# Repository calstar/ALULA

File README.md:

# ALULA (LE2)
 Alula/ LE2 Hot-fire and Flight Vehicle Electronics Control

## Summary
**DAQboard.ino** file commands the ESP32 that reads data from sensors and commands from the COM Board, and sends data in a package to the COM Board.

**COMBoard.ino** file commands the ESP32 that receives data in a package from the DAQ  Board, sends commands to the DAQ Board, and sends data to MATLAB for plotting and data-saving purposes through the serial port.

**liveplot.m** is a MATLAB file that can receive data from the COM Board, create live plots, and save the data.
  1. **Change the test file name according to the trial number in the liveplot.m file.**
  2. Click "Run" to start the code, and close the plotting window to stop the code. Test data will be automatically stored in a spreadsheet under a folder called "**Test_Data_yyyy-mm-dd**."

## ESP32 MAC Addresses
- DAQ Breadboard:{0x24, 0x62, 0xAB, 0xD2, 0x85, 0xDC}
- COM Breadboard:{0xC4, 0xDD, 0x57, 0x9E, 0x91, 0x6C};
- DAQ Protoboard:

## Software requirement
**Ctrl click (Windows) or Cmd click the following links to open them in new tabs**
1. Arduino (https://www.arduino.cc/en/software)
2. MATLAB (https://software.berkeley.edu/matlab®)
    - To control the serial port, you need to install the [**Instrument Control Toolbox**](https://www.mathworks.com/products/instrument.html).
3. (optional) An external code editing software such as Atom (https://atom.io) or Visual Studio (https://visualstudio.microsoft.com/downloads/).
    - Arduino IDE and MATLAB are sufficient for all the coding
4. (recommended) GitHub Desktop (https://desktop.github.com). You can pull, push, and edit files with ease. **Step 3 required if you would like to download GitHub Desktop as the software requires an external editor.**

## How to contribute

### Using Git (recommended)
CLONE USING: 
```git clone --recurse-submodules git@github.com:calstar/LE2.git``` 

Please refer to https://rocketry.gitbook.io/public/tutorials/avionics/git-and-workflow for more information.

A basic workflow might go as follows:

`git status` 

`git add .` 

`git status` Note: if you see files here that are not code/hardware and should not be added (binaries, images, autosave files, etc.), STOP and fix the `.gitignore` 

`git commit -m "[Descriptive commit message of what you changed]"` 

`git push` 

### Using Github Desktop (not recommended)
1. Make sure you have access to this project
    - Check with you administrators
2. Go to the Github app, sign in, and click on the top left corner. You should see a pop-up window with an "Add" button. Select that button and choose "Clone repository."
3. Search in "Filter you repositories" using the keyword "ellie-ground." Select the correct repository and click "Clone."
    - If you want this cloned repository to be in a different folder, change the "Local Path."
4. After you have edited and saved the file in the local repository, GitHub Desktop will detect changes and prompt you to commit. Make sure to double check your changes before committing.
5. On the bottom left corner, put down a short summary that describes what you have changed, then click "Commit to **main**."
6. In the middle of the screen (or on the top banner) you will see "Push commits to the origin remote." If you are sure that the commit is ready, click "Push origin."
6. Check the project online and see if the changes have been reflected.

## Helpful resources
### ESP32-DevkitC/ ESP32-Devkit-v4 (for PCB application - antenna sticks out of board)
Getting started

https://docs.espressif.com/projects/esp-idf/en/latest/esp32/hw-reference/esp32/get-started-devkitc.html

Pinout reference

### ESP32-WROOM/ ESP32-Devkit-v1 (for breadboard/protoboard application - antenna does NOT stick out of board)

Pinout reference

### ESP32-HUZZAH (for breadboard/protoboard application)

Pinout reference

### Pressure transducer color code
Red - E+

Black - E-

Green - A-

White - A+

Other possible combinations: Blue E+; Red E-; Green A-; Black A+

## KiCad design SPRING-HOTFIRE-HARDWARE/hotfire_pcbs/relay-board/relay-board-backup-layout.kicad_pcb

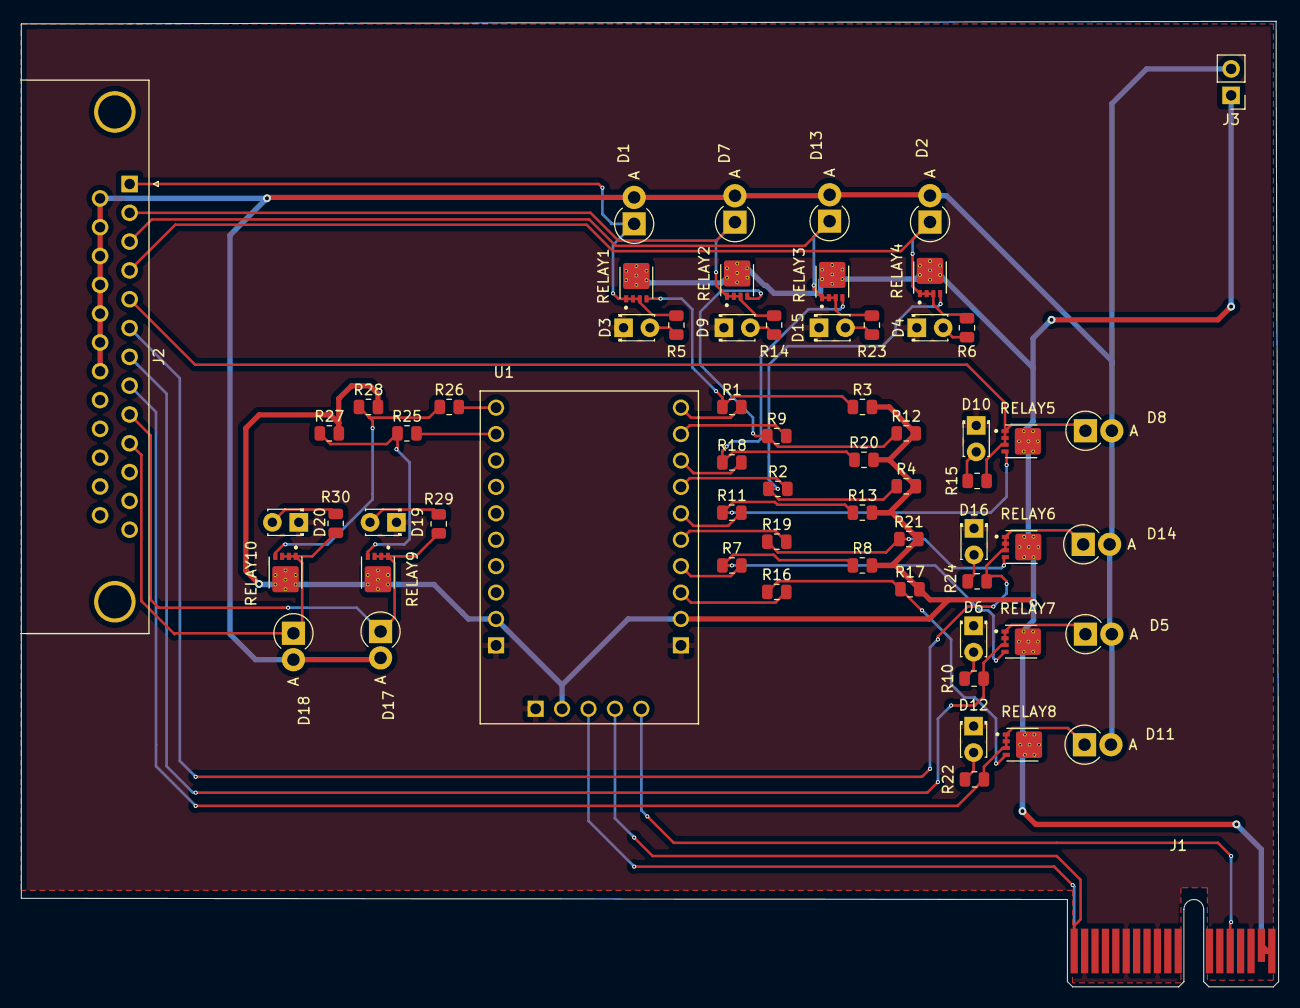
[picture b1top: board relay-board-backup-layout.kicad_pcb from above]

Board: 2 copper layers, 120.9 x 92.8 mm, 64 parts (0 on the bottom side), 47 nets.

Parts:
D1, D2, D5, D7, D8, D11, D13, D14, D17, D18: D_Small; D_DO-15_P2.54mm_Vertical_AnodeUp
D3, D4, D6, D9, D10, D12, D15, D16, D19, D20: LED; LED_D1.8mm_W3.3mm_H2.4mm
J1: PCIE_CONN; BUS_PCIexpress_x1
J2: DB25_Female; DSUB-25_Male_Horizontal_P2.77x2.84mm_EdgePinOffset7.70mm_Ho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
J3: 12V LiPO; PinHeader_1x02_P2.54mm_Vertical
R1, R2, R7, R9, R11, R16, R18, R19, R25, R26: 100; R_0805_2012Metric
R3, R4, R8, R12, R13, R17, R20, R21, R27, R28: 10k; R_0805_2012Metric
R5, R6, R10, R14, R15, R22, R23, R24, R29, R30: 330; R_0805_2012Metric
RELAY1, RELAY2, RELAY3, RELAY4, RELAY5, RELAY6, RELAY7, RELAY8, RELAY9, RELAY10: CSD25402Q3AT; TRANS_CSD25402Q3AT
U1: PCF8575_Breakout

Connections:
+3.3V: J1.B17 (Pin_b17), J1.B18 (Pin_b18)
+5V: J1.A17 (Pin_a17), J1.A18 (Pin_a18), J3.1, R3.2, R4.2, R8.2, R12.2, R13.2, R17.2, R20.2, R21.2, R27.2, R28.2, RELAY1.9, RELAY1.9_1, RELAY1.9_2, RELAY1.9_3, RELAY1.9_4, RELAY1.9_5, RELAY1.9_6, RELAY1.9_7, RELAY2.9, RELAY2.9_1, RELAY2.9_2, RELAY2.9_3, RELAY2.9_4, RELAY2.9_5, RELAY2.9_6, RELAY2.9_7, RELAY3.9, RELAY3.9_1, RELAY3.9_2, RELAY3.9_3, RELAY3.9_4, RELAY3.9_5, RELAY3.9_6, RELAY3.9_7, RELAY4.9, RELAY4.9_1, RELAY4.9_2, RELAY4.9_3, RELAY4.9_4, RELAY4.9_5, RELAY4.9_6, RELAY4.9_7, RELAY5.9, RELAY5.9_1, RELAY5.9_2, RELAY5.9_3, RELAY5.9_4, RELAY5.9_5, RELAY5.9_6, RELAY5.9_7, RELAY6.9, RELAY6.9_1, RELAY6.9_2, RELAY6.9_3, RELAY6.9_4, RELAY6.9_5, RELAY6.9_6, RELAY6.9_7, RELAY7.9, RELAY7.9_1, RELAY7.9_2, RELAY7.9_3, RELAY7.9_4, RELAY7.9_5, RELAY7.9_6, RELAY7.9_7, RELAY8.9, RELAY8.9_1, RELAY8.9_2, RELAY8.9_3, RELAY8.9_4, RELAY8.9_5, RELAY8.9_6, RELAY8.9_7, RELAY9.9, RELAY9.9_1, RELAY9.9_2, RELAY9.9_3, RELAY9.9_4, RELAY9.9_5, RELAY9.9_6, RELAY9.9_7, RELAY10.9, RELAY10.9_1, RELAY10.9_2, RELAY10.9_3, RELAY10.9_4, RELAY10.9_5, RELAY10.9_6, RELAY10.9_7, U1.9 (VDD), U1.12 (VCC), U1.17 (VDD)
/-7V: D1.2 (A), D2.2 (A), D5.2 (A), D7.2 (A), D8.2 (A), D11.2 (A), D13.2 (A), D14.2 (A), D17.2 (A), D18.2 (A), J2.14, J2.15, J2.16, J2.17, J2.18, J2.19, J2.20, J2.21, J2.22, J3.2
GND: D3.1 (K), D4.1 (K), D6.1 (K), D9.1 (K), D10.1 (K), D12.1 (K), D15.1 (K), D16.1 (K), D19.1 (K), D20.1 (K), J1.A2 (Pin_a2), J1.A5 (Pin_a5), J1.A8 (Pin_a8), J1.A11 (Pin_a11), J1.A15 (Pin_a15), J1.B2 (Pin_b2), J1.B6 (Pin_b6), J1.B9 (Pin_b9), J1.B12 (Pin_b12), J1.B16 (Pin_b16), U1.10 (GND), U1.11 (GND), U1.16 (GND)
unnamed: D3.2 (A), R5.2
unnamed: D4.2 (A), R6.2
unnamed: D6.2 (A), R10.2
unnamed: D9.2 (A), R14.2
unnamed: D10.2 (A), R15.2
unnamed: D12.2 (A), R22.2
unnamed: D15.2 (A), R23.2
unnamed: D16.2 (A), R24.2
unnamed: D19.2 (A), R29.2
unnamed: D20.2 (A), R30.2
unnamed: R1.1, R3.1, RELAY1.4
unnamed: R2.1, R4.1, RELAY4.4
unnamed: R7.1, R8.1, RELAY7.4
unnamed: R9.1, R12.1, RELAY2.4
unnamed: R11.1, R13.1, RELAY5.4
unnamed: R16.1, R17.1, RELAY8.4
unnamed: R18.1, R20.1, RELAY3.4
unnamed: R19.1, R21.1, RELAY6.4
unnamed: R25.1, R27.1, RELAY9.4
unnamed: R26.1, R28.1, RELAY10.4
RELAY1: D1.1 (K), J2.1, R5.1, RELAY1.1, RELAY1.2, RELAY1.3
RELAY2: D7.1 (K), J2.2, R14.1, RELAY2.1, RELAY2.2, RELAY2.3
RELAY3: D13.1 (K), J2.3, R23.1, RELAY3.1, RELAY3.2, RELAY3.3
RELAY4: D2.1 (K), J2.4, R6.1, RELAY4.1, RELAY4.2, RELAY4.3
RELAY5: D8.1 (K), J2.5, R15.1, RELAY5.1, RELAY5.2, RELAY5.3
RELAY6: D14.1 (K), J2.6, R24.1, RELAY6.1, RELAY6.2, RELAY6.3
RELAY7: D5.1 (K), J2.7, R10.1, RELAY7.1, RELAY7.2, RELAY7.3
RELAY8: D11.1 (K), J2.8, R22.1, RELAY8.1, RELAY8.2, RELAY8.3
RELAY9: D17.1 (K), J2.9, R29.1, RELAY9.1, RELAY9.2, RELAY9.3
RELAY10: D18.1 (K), J2.10, R30.1, RELAY10.1, RELAY10.2, RELAY10.3
RL INT: J1.B14 (Pin_b14), U1.15 (INT)
RL SCL: J1.B1 (Pin_b1), U1.14 (SCL)
RL SDA: J1.A1 (Pin_a1), U1.13 (SDA)
SIGNAL1: R1.2, U1.25 (P07)
SIGNAL2: R9.2, U1.24 (P06)
SIGNAL3: R18.2, U1.23 (P05)
SIGNAL4: R2.2, U1.22 (P04)
SIGNAL5: R11.2, U1.21 (P03)
SIGNAL6: R19.2, U1.20 (P02)
SIGNAL7: R7.2, U1.19 (P01)
SIGNAL8: R16.2, U1.18 (P00)
SIGNAL9: R25.2, U1.2 (P11)
SIGNAL10: R26.2, U1.1 (P10)

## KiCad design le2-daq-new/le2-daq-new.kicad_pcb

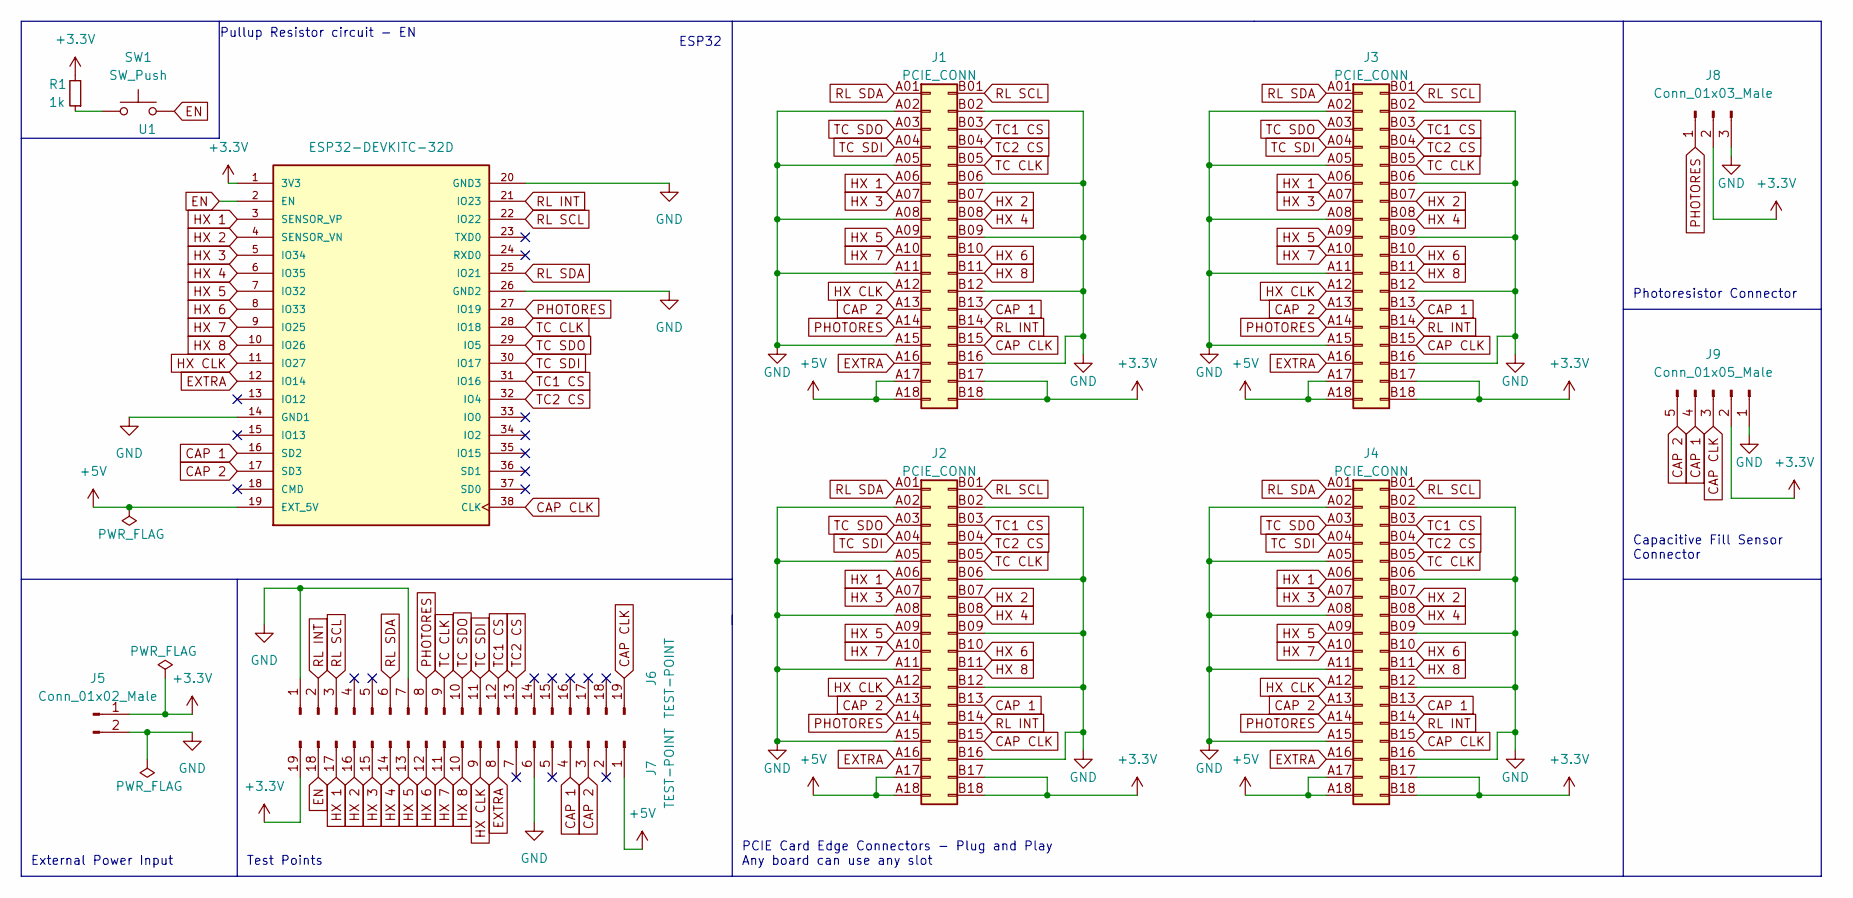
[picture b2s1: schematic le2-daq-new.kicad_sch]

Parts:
J1, J2, J3, J4: PCIE_CONN; AMPHENOL_10018784-10210TLF
J5: Conn_01x02_Male; PinHeader_1x02_P2.54mm_Vertical
J6, J7: TEST-POINT; PinHeader_1x19_P2.54mm_Vertical
J8: Conn_01x03_Male; PinHeader_1x03_P2.54mm_Vertical
J9: Conn_01x05_Male; PinHeader_1x05_P2.54mm_Vertical
R1: 1k; R_0805_2012Metric_Pad1.20x1.40mm_HandSolder
SW1: SW_Push; SolderJumper-2_P1.3mm_Bridged2Bar_Pad1.0x1.5mm
U1: ESP32-DEVKITC-32D; MODULE_ESP32-DEVKITC-32D; PARTREV 4

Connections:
+3.3V: J1.B17 (Pin_b17), J1.B18 (Pin_b18), J2.B17 (Pin_b17), J2.B18 (Pin_b18), J3.B17 (Pin_b17), J3.B18 (Pin_b18), J4.B17 (Pin_b17), J4.B18 (Pin_b18), J5.1, J7.19, J8.2, J9.2, R1.2, U1.1 (3V3)
+5V: J1.A17 (Pin_a17), J1.A18 (Pin_a18), J2.A17 (Pin_a17), J2.A18 (Pin_a18), J3.A17 (Pin_a17), J3.A18 (Pin_a18), J4.A17 (Pin_a17), J4.A18 (Pin_a18), J7.1, U1.19 (EXT_5V)
CAP 1: J1.B13 (Pin_b13), J2.B13 (Pin_b13), J3.B13 (Pin_b13), J4.B13 (Pin_b13), J7.4, J9.4, U1.16 (SD2)
CAP 2: J1.A13 (Pin_a13), J2.A13 (Pin_a13), J3.A13 (Pin_a13), J4.A13 (Pin_a13), J7.3, J9.5, U1.17 (SD3)
CAP CLK: J1.B15 (Pin_b15), J2.B15 (Pin_b15), J3.B15 (Pin_b15), J4.B15 (Pin_b15), J6.19, J9.3, U1.38 (CLK)
EN: J7.18, SW1.2, U1.2 (EN)
EXTRA: J1.A16 (Pin_a16), J2.A16 (Pin_a16), J3.A16 (Pin_a16), J4.A16 (Pin_a16), J7.8, U1.12 (IO14)
GND: J1.A02 (Pin_a2), J1.A05 (Pin_a5), J1.A08 (Pin_a8), J1.A11 (Pin_a11), J1.A15 (Pin_a15), J1.B02 (Pin_b2), J1.B06 (Pin_b6), J1.B09 (Pin_b9), J1.B12 (Pin_b12), J1.B16 (Pin_b16), J2.A02 (Pin_a2), J2.A05 (Pin_a5), J2.A08 (Pin_a8), J2.A11 (Pin_a11), J2.A15 (Pin_a15), J2.B02 (Pin_b2), J2.B06 (Pin_b6), J2.B09 (Pin_b9), J2.B12 (Pin_b12), J2.B16 (Pin_b16), J3.A02 (Pin_a2), J3.A05 (Pin_a5), J3.A08 (Pin_a8), J3.A11 (Pin_a11), J3.A15 (Pin_a15), J3.B02 (Pin_b2), J3.B06 (Pin_b6), J3.B09 (Pin_b9), J3.B12 (Pin_b12), J3.B16 (Pin_b16), J4.A02 (Pin_a2), J4.A05 (Pin_a5), J4.A08 (Pin_a8), J4.A11 (Pin_a11), J4.A15 (Pin_a15), J4.B02 (Pin_b2), J4.B06 (Pin_b6), J4.B09 (Pin_b9), J4.B12 (Pin_b12), J4.B16 (Pin_b16), J5.2, J6.1, J6.7, J7.6, J8.3, J9.1, U1.14 (GND1), U1.20 (GND3), U1.26 (GND2)
HX 1: J1.A06 (Pin_a6), J2.A06 (Pin_a6), J3.A06 (Pin_a6), J4.A06 (Pin_a6), J7.17, U1.3 (SENSOR_VP)
HX 2: J1.B07 (Pin_b7), J2.B07 (Pin_b7), J3.B07 (Pin_b7), J4.B07 (Pin_b7), J7.16, U1.4 (SENSOR_VN)
HX 3: J1.A07 (Pin_a7), J2.A07 (Pin_a7), J3.A07 (Pin_a7), J4.A07 (Pin_a7), J7.15, U1.5 (IO34)
HX 4: J1.B08 (Pin_b8), J2.B08 (Pin_b8), J3.B08 (Pin_b8), J4.B08 (Pin_b8), J7.14, U1.6 (IO35)
HX 5: J1.A09 (Pin_a9), J2.A09 (Pin_a9), J3.A09 (Pin_a9), J4.A09 (Pin_a9), J7.13, U1.7 (IO32)
HX 6: J1.B10 (Pin_b10), J2.B10 (Pin_b10), J3.B10 (Pin_b10), J4.B10 (Pin_b10), J7.12, U1.8 (IO33)
HX 7: J1.A10 (Pin_a10), J2.A10 (Pin_a10), J3.A10 (Pin_a10), J4.A10 (Pin_a10), J7.11, U1.9 (IO25)
HX 8: J1.B11 (Pin_b11), J2.B11 (Pin_b11), J3.B11 (Pin_b11), J4.B11 (Pin_b11), J7.10, U1.10 (IO26)
HX CLK: J1.A12 (Pin_a12), J2.A12 (Pin_a12), J3.A12 (Pin_a12), J4.A12 (Pin_a12), J7.9, U1.11 (IO27)
unnamed: R1.1, SW1.1
PHOTORES: J1.A14 (Pin_a14), J2.A14 (Pin_a14), J3.A14 (Pin_a14), J4.A14 (Pin_a14), J6.8, J8.1, U1.27 (IO19)
RL INT: J1.B14 (Pin_b14), J2.B14 (Pin_b14), J3.B14 (Pin_b14), J4.B14 (Pin_b14), J6.2, U1.21 (IO23)
RL SCL: J1.B01 (Pin_b1), J2.B01 (Pin_b1), J3.B01 (Pin_b1), J4.B01 (Pin_b1), J6.3, U1.22 (IO22)
RL SDA: J1.A01 (Pin_a1), J2.A01 (Pin_a1), J3.A01 (Pin_a1), J4.A01 (Pin_a1), J6.6, U1.25 (IO21)
TC1 CS: J1.B03 (Pin_b3), J2.B03 (Pin_b3), J3.B03 (Pin_b3), J4.B03 (Pin_b3), J6.12, U1.31 (IO16)
TC2 CS: J1.B04 (Pin_b4), J2.B04 (Pin_b4), J3.B04 (Pin_b4), J4.B04 (Pin_b4), J6.13, U1.32 (IO4)
TC CLK: J1.B05 (Pin_b5), J2.B05 (Pin_b5), J3.B05 (Pin_b5), J4.B05 (Pin_b5), J6.9, U1.28 (IO18)
TC SDI: J1.A04 (Pin_a4), J2.A04 (Pin_a4), J3.A04 (Pin_a4), J4.A04 (Pin_a4), J6.11, U1.30 (IO17)
TC SDO: J1.A03 (Pin_a3), J2.A03 (Pin_a3), J3.A03 (Pin_a3), J4.A03 (Pin_a3), J6.10, U1.29 (IO5)

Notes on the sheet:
Capacitive Fill Sensor Connector
Pullup Resistor circuit - EN
Test Points
ESP32
Photoresistor Connector
External Power Input
PCIE Card Edge Connectors - Plug and Play Any board can use any slot

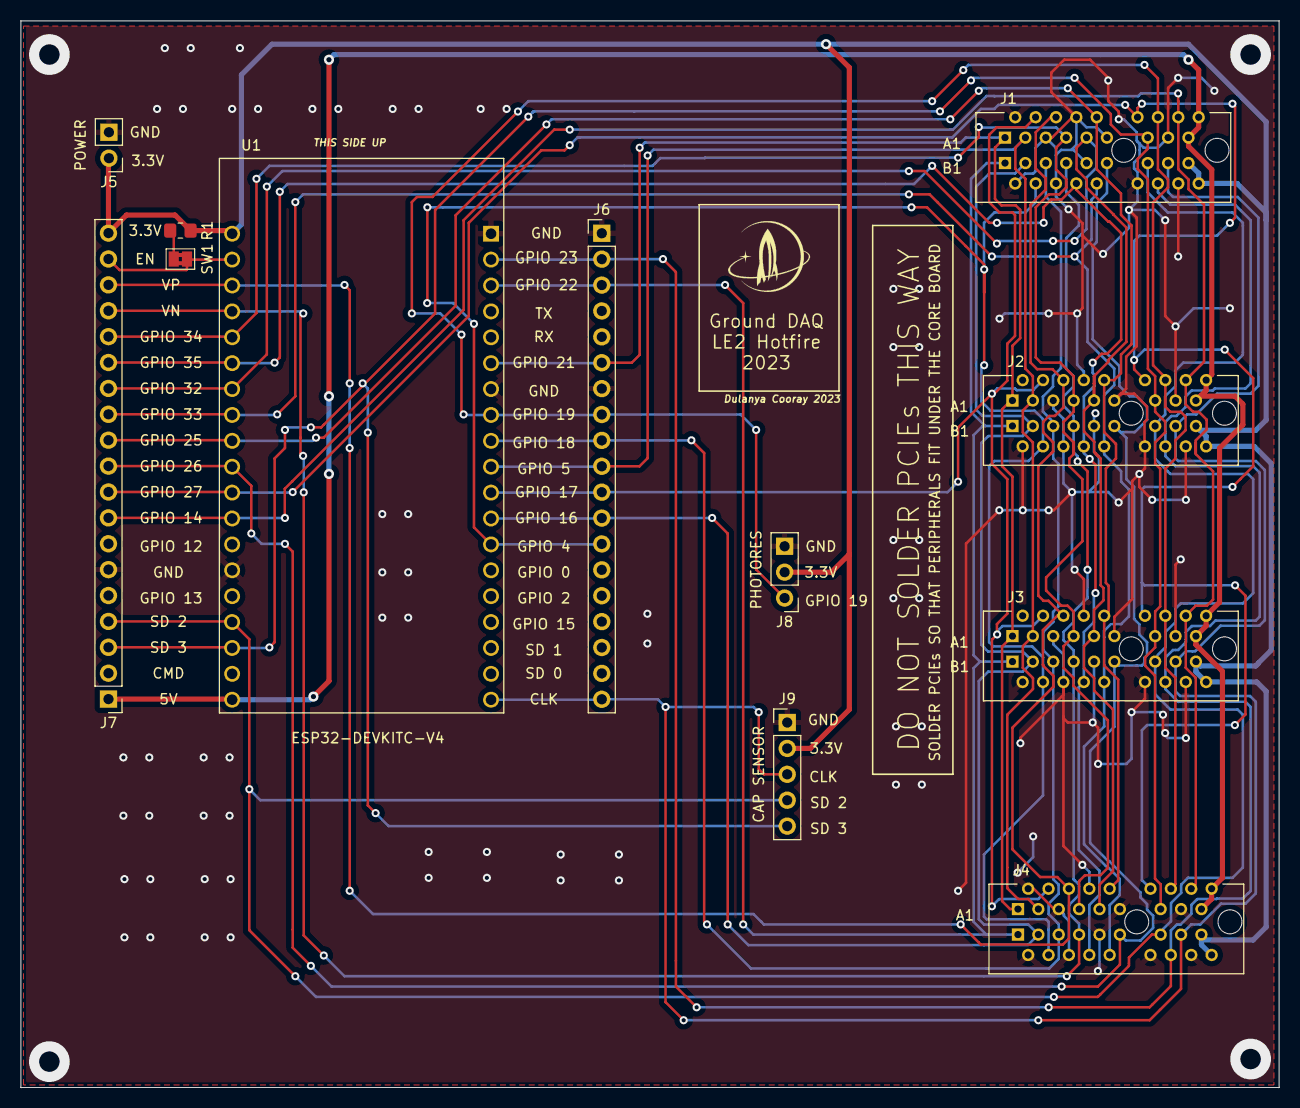
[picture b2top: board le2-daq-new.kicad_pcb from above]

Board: 2 copper layers, 123.4 x 104.6 mm, 12 parts (0 on the bottom side), 27 nets.

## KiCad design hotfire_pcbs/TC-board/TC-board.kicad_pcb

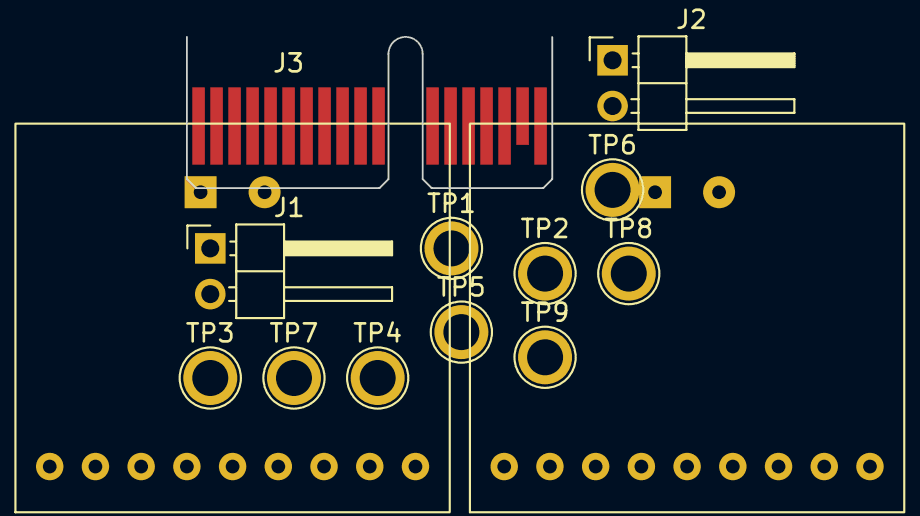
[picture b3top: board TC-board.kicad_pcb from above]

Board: 2 copper layers, 14 parts (0 on the bottom side), 11 nets, no tracks yet.

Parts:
J1, J2: JST; PinHeader_1x02_P2.54mm_Horizontal
J3: PCIE-LP-01-01-F-DV-A-TR; BUS_PCIexpress_x1
TP1, TP2, TP3, TP4, TP5, TP6, TP7, TP8, TP9: TestPoint; TestPoint_Plated_Hole_D2.0mm
U1, U2: MAX31856_Breakout

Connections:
+3V3: J3.B17, J3.B18, U1.11 (VIN), U2.11 (VIN)
/SPI_CS_0: J3.B3, TP8.1, U1.5 (CS)
/SPI_CS_1: J3.B4, TP9.1, U2.5 (CS)
/SPI_MISO: J3.A3, TP5.1, U1.7 (SDO), U2.7 (SDO)
/SPI_MOSI: J3.A4, TP6.1, U1.6 (SDI), U2.6 (SDI)
/SPI_SCK: J3.B5, TP7.1, U1.8 (SCK), U2.8 (SCK)
/TC1_T+: J1.2, TP2.1, U1.2 (T+)
/TC1_T-: J1.1, TP1.1, U1.1 (T-)
/TC2_T+: J2.2, TP4.1, U2.2 (T+)
/TC2_T-: J2.1, TP3.1, U2.1 (T-)
GND: J3.A2, J3.A5, J3.A8, J3.A11, J3.A15, J3.A18, J3.B2, J3.B6, J3.B9, J3.B12, J3.B16, U1.9 (GND), U2.9 (GND)

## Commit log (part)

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2023-06-20 reorganized simulation stuff
2023-06-21 Inaccurate
2023-06-24 updated pcb designs
2023-06-25 flught sim
2023-06-25 added integration code
2023-06-25 skeletal for guesstimator
2023-06-26 Updated flight sim
2023-06-26 .eng file header updated
2023-07-02 Add files via upload
    implemented vers
2023-07-20 liam_thrustcurve
    Working on thrust curve convergent model
2023-07-22 Fixed Thrust Curve
    Solved Convergence
    Added failure errors for flow instability - baseline 10% pressure drop requirement
2023-07-22 Added GN2
    Gamma = Cp/Cv
2023-07-24 feed system resistance
2023-07-24 main input
2023-07-24 .eng attempt. Still not writing array to file
2023-07-24 write to .eng file fix
2023-08-01 .eng fixed
2023-08-05 Liquid flight sim
2023-08-06 files
2023-08-06 SD read write
2023-08-06 SD card read write
2023-08-08 Updated parameters & thrust curve
2023-08-14 updates for file overwrite, and also massive increase in chamber pressure
2023-08-14 total impulse numerical estimate added
2023-08-24 Add files via upload
    Collapse_Integration.py contains the collapse function for LOX & ETH using N2 as pressurant
    Thrust_Conv_with_Collapse calls that function (as an import from the other file) so you need both files on your device to run it all together
2023-09-22 need analysis_parameters update
2023-09-23 made a new fall23hotfire folder which is a copy of the spring23 folder
2023-09-23 test fix
2023-09-27 Updated total mass calc
2023-09-28 Add files via upload
    Updated thrust
2023-10-01 calibration and python code structure
2023-10-02 sync
2023-10-02 Fixed wifidebug bug.
2023-10-03 avg filtering
2023-10-03 Changed DAQ and PT calibration code.
2023-10-04 Fixed pcf errors
2023-10-05 ptcal
2023-10-06 update PT_cal
2023-10-06 random things plus calibration. Test 8 is accurate cal for hx2
2023-10-06 python cal clarity
2023-10-06 ;aldifj
2023-10-06 DONE
2023-10-06 live plot updated
2023-10-06 newww live
2023-10-07 updated PTcal
2023-10-07 added daq delay
2023-10-07 Hotfire calibration
2023-10-07 daq change w/liam
2023-10-07 latest
2023-10-11 Add sampling code and wrap some functions
    (not finished + kinda messy w/ ipynb format)
2023-10-13 small context changes
2023-10-24 Update DAQBoard_LE2.ino
    Created function inside struct that contains data to compute a rolling average of sensor readings - Ishir, Vidushi
2023-10-24 Add files via upload
    Test script for rolling average function with spoof data
2023-10-25 labview
2023-10-27 Bug fix: updating last reading variable
2023-10-28 Added wrapper classes for data collection boards
2023-10-28 Refactored code to work with new data reading functions
2023-10-31 conda env for flight sim
2023-11-03 calibration org
2023-11-03 Tested filter on ESP32, succesfully filters out spikes
2023-11-06 daq changes pii assignments for pcf
2023-11-06 Fixed queue so it pushes out old elements in favor of new ones At 20 ms read delay, queue is able to clear itself, but at 15 ms it is NOT able to; not sure if this will change over longer distances A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
2023-11-07 Clears queue when queue is full
2023-11-07 pt calibration 11/7/23
2023-11-07 Added filter and new queue functionality into COM DAQ code
2023-11-07 debug
2023-11-08 reverted to 5thNov commit to do mosfet testing, changed GPIO pins
2023-11-10 state adjustments
2023-11-11 TC Test Code
2023-11-14 11_13_2023 PT calibration
2023-11-14 abort changes just safety and turning off igniter
2023-11-15 Filtered version of DAQ code
2023-11-15 Removed pressComplete variable. updated mosfet serial command test.
2023-11-15 Tested filter code in DEBUG mode, still needs to be tested with sensors
2023-11-16 added tc_cal folder
2023-11-16 Com daq bug fixes with python gui
2023-11-16 bug fix
2023-11-16 update tc_cal
2023-11-16 changed broadcast addresses
2023-11-16 added other TCs
2023-11-16 pt cal garage
2023-11-16 Fixed pinouts from 11/15/23 testing
2023-11-17 11/17 cal
2023-11-17 pt hx2 cal
2023-11-17 tc cal
2023-11-18 Added tc3 and tc4
2023-11-18 fix press valves staying on in debug
2023-11-18 UPdated PT calibration parameters from 11/17
2023-11-18 added calibration, gain proper, and polyfit code
2023-11-18 fixed lc3&4
2023-11-18 old liveplot removed
2023-11-18 syntax
2023-11-18 final calibration
2023-11-18 python gui code
2023-11-18 Python gui code update
2023-11-18 pressures
2023-11-18 Moved LC combined plot
2023-11-18 lc raw values only read to com
2023-11-18 fixed parameter
2023-11-18 tested com + python gui code
2023-11-19 11/18 HOTFIRE DATA
2023-11-19 filtered was hotfire code
2023-11-19 Data from failed hotfire attempt 11/18
2023-11-26 analysis start
2023-11-27 excel cahnges
2023-11-28 python gui update
2024-01-08 regen
    setup for dev, script setup
2024-01-25 testedits
2024-01-27 valvesim
2024-01-27 reorg
2024-01-27 powersenseseparation
2024-01-28 gearmotordriver
2024-01-30 Update DAQ_POWER.ino without sensors and median filter
2024-01-30 Update DAQ_SENSE with commented out power and state machine
2024-02-01 DAQ Power and Sense code finished (STILL UNTESTED)
2024-02-01 Finished initial COM script for 3-way comm NOT TESTED YET
2024-02-01 vidushi's daq sense and power code
2024-02-02 edits for 3-way coms
2024-02-03 send commits
2024-02-03 fixes
2024-02-04 snese fix
2024-02-04 dwbug
2024-02-04 updated daq sense
2024-02-04 delays
2024-02-04 EDITS FOR CONTROL, SERIAL PARSE
2024-02-04 control authority given to user in abort
2024-02-04 structures
2024-02-06 mac updates
2024-02-06 updated com
2024-02-09 macs
2024-02-09 changed COM mac addy
2024-02-09 mosfet fixes
2024-02-10 quick fixes
2024-02-10 Calibration Code + Coefficients
2024-02-10 updated abaort
2024-02-10 times
2024-02-11 power
2024-02-11 daq power
2024-02-11 test
2024-02-12 state adjusts
    aborts added
2024-02-12 mac for com
2024-02-12 kljdsf
2024-02-13 new press() function that shouldnt stop pressing upon receiving a noise spike
2024-02-13 timer fixes
2024-02-13 readrate
2024-02-13 neeew liveee
2024-02-19 Adding calibration csvs
2024-02-24 Create Thrust Curve Supplemental Files
2024-02-28 aksj
2024-02-28 hx troubles :(
2024-02-28 calibration hx2
2024-02-28 power thresholds for lp test
2024-02-29 Leak Test + PT constants
2024-02-29 update com code
2024-02-29 wifidebug if
2024-03-01 HEHEHE
2024-03-01 pressure flags
2024-03-01 ETH/OX DONEEEE
2024-03-02 TESTING
2024-03-02 com getting both power and sense source. currently reading sense
2024-03-02 fixed constant wifi attempts
2024-03-02 Broadcast address update
2024-03-02 calibration
2024-03-04 HOTFIRE DATA
2024-03-05 Hotfire changes and updates to sense timing
2024-03-05 analysis
2024-03-09 Updated hotfire code
2024-03-09 massflow from hotfire1
2024-03-09 OF Ratio Calcs
2024-03-09 recalc
2024-03-10 hotfire 2 analysis
2024-03-10 hf data analysis
2024-03-10 more mass flow analysis
2024-03-13 State machine for launch
2024-03-13 State machine update for launch
2024-03-17 1. Abort only activates after a set amount of time of pressure being too high 2. Sends both filtered and raw readings
2024-03-20 FlightBoard edits for abort actuation, name conventions
2024-03-20 update to serial print readings
2024-03-20 testing, org, fetch serial
2024-03-22 print statements for debugging usb
2024-03-22 setup description
2024-03-23 updated pinouts for flight
2024-03-23 directions for running
2024-03-23 getreadings
2024-03-23 valves off
2024-03-31 Bug fixes
2024-04-02 pt calibration pinouts updated
2024-04-10 fixed autoabort delay, and tested 3-way comm structure
2024-04-14 regen
2024-04-15 com communication for abort
2024-04-15 updated pinouts
2024-04-16 half second abort delay' did not match any files
2024-04-16 Added ability for Flight to initiate Abort sequence (THIS IS UNTESTED)
2024-04-16 Implemented writing to SD card
2024-04-16 SD card doesn't write in Idle now
2024-04-18 flight sends bool to COM indicating whether SD card file successfully opened
2024-04-18 SD card periodically flushes based on set time interval
2024-04-18 daq and flight now send to all boards simultaneously
2024-04-19 discharge calcs
2024-04-19 tested flight
2024-04-19 daq testest
2024-04-19 cleanup and restore pins on flight
2024-04-19 fixed abort
2024-04-19 restore gpio initialization
2024-04-19 cleanup
2024-04-19 offset reset during idle initiate
2024-04-20 flight
2024-04-20 fixes to pcf
2024-04-20 testing with open mosfets
2024-04-20 gains
2024-04-21 COMM
2024-04-21 COM WORKING??
2024-04-21 extra PT, maybe fixed pin 5 issue?
2024-04-21 com flight issues fixed
2024-04-21 three way comms
2024-04-21 three way comms - DAQ
2024-04-21 flight adjustments
2024-04-22 DAQ COM communication not working rn, COM Flight mostly works but won't return to idle
2024-04-22 read above commit, daq changes here
2024-04-22 flight board edits to comms structure, debug states
2024-04-22 edits to gui to remove lcs, reset tc plotting. needs edits
2024-04-22 resistance
2024-04-22 com's daqstate difference recognition
2024-04-22 dumbed down daq send. works
2024-04-22 debugs
2024-04-22 Changes to FlightBoard for WIFI debug
2024-04-22 Changed position of sizeof(sendCommands so that it always prints in debug state
2024-04-22 Update DAQ.ino
    removed duplicate syncdaqstates
2024-04-23 working com
2024-04-23 added pt_x
2024-04-23 Update DAQ.ino
    Fixed DAQ Code
2024-04-23 debug cleanup, correct send signature assignment
2024-04-23 auto abort fix
2024-04-23 Make sure that CDC is enabled
2024-04-23 updated sd card code
2024-04-23 debug setup for simulaiton of press
2024-04-23 updated sd card code; no need for periodic flush because flush time is neglible
2024-04-23 SD card working finally
2024-04-23 Update FlightBoard.ino
    TOOK OUT WHILE(!SERIAL)
2024-04-23 Update FlightBoard.ino
    got rid of while serial
2024-04-23 Working.. for now
2024-04-23 edited print format
2024-04-23 WORKING ON QD LOGIC
2024-04-23 qd logic
    qd logic
2024-04-23 pt calibration main redone pinouts
2024-04-23 temperature dependency comparisons
2024-04-23 suppress print statements in sd card write function with wifidebug
2024-04-24 temperature dependency copy
2024-04-24 pinout update
2024-04-24 Complete lora comm code (untested)
2024-04-24 FIX QD
2024-04-24 16 -> 18?
2024-04-24 Calibrated core boards 1 and 2
2024-04-25 removed TC
2024-04-25 flight sends to both at once to avoid delay
2024-04-25 updated COM serial printout
2024-04-25 updated gui
2024-04-25 mac address on com
2024-04-25 solenoids working
2024-04-25 remote structure setup
2024-04-25 completed com for remote offset changes
2024-04-25 updated command gui for remote offset changes
2024-04-25 WORKING REMOTE OFFSET CHANGES
2024-04-25 revert
2024-04-25 wip
    rebase
2024-04-25 pt calibrations and linear offset proof
2024-04-26 constants
2024-04-27 updated mac
2024-04-27 updated gui with zero offset button, and mac
2024-04-27 gui with zero offset button working
2024-04-27 add declaration for SD
2024-04-28 flight send to conor board
2024-04-28 conor board mac address added
2024-04-28 updated gui with led for abort and press complete
2024-04-28 code for foolproof sd card solution
2024-04-28 mac for flight
2024-04-28 SDCard working?
2024-04-28 SDCARD
2024-04-28 remove all auto abort functionality for REDS system
2024-04-28 daq constants
2024-05-01 lowpresstest
2024-05-01 state machine manual debug
2024-05-08 Changed pin out for PT-X so that it works
2024-05-11 commit long range com
2024-05-14 Calibrated Core A
2024-05-14 Re added abort on flight and deleted typos in comboard
2024-05-14 Changed slopes
2024-05-14 NEW CODE
2024-05-16 Tested LR com-flight and Low pressure tested
2024-05-16 Calibrated CORE ABC
2024-05-17 brought back abort
2024-05-17 flight board updates ... polyfit, median filtering, abort thresholds
2024-05-17 optimize?
2024-05-17 button dynamics
2024-05-18 light buttons
2024-05-18 layout rearrange
2024-05-18 button reverted to press indications
2024-05-18 WORKING
2024-05-19 updates to gui communication. daq mac address update after fried board
2024-05-19 mac, 100psi press
2024-05-19 send delay
2024-05-19 sd card
2024-05-19 mac address, and daq abort fix
2024-05-23 flight!
2024-09-17 Create PT_CALIBRATION_TEST.py
    PT test 9/17
2024-09-17 PT test 9/17
2024-09-27 calibration 9/18
